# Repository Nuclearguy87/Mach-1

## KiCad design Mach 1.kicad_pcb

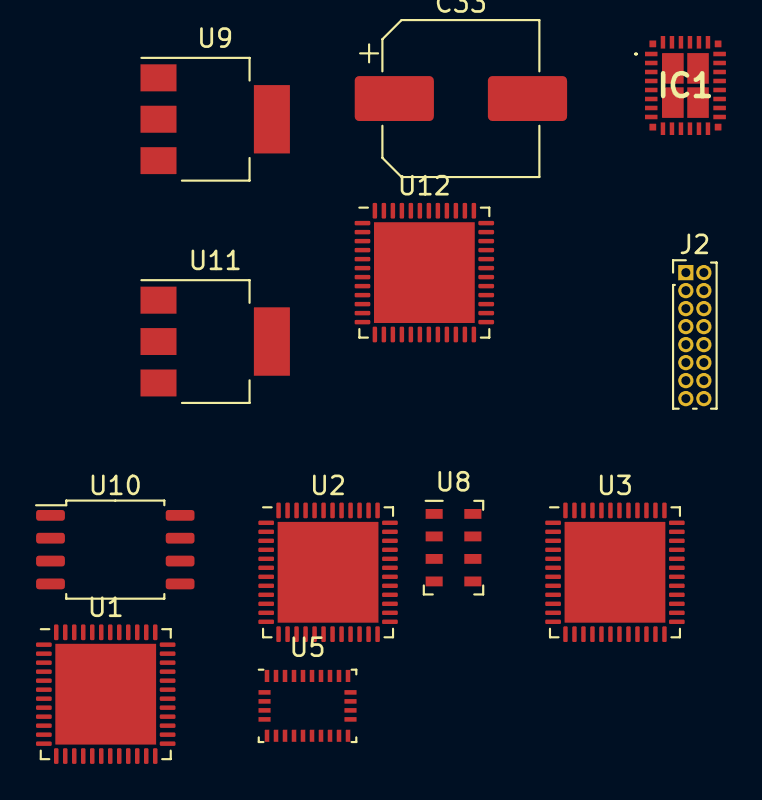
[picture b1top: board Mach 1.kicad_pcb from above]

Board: 2 copper layers, 12 parts (0 on the bottom side), 13 nets, no tracks yet.

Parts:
C33: 220m; CP_Elec_8x10.5
IC1: LT8638SJV#TRPBF; LT8638SJVTRPBF
J2: Conn_02x08_Counter_Clockwise; PinHeader_2x08_P1.00mm_Vertical
U1: STM32U575CIU6Q; QFN-48-1EP_7x7mm_P0.5mm_EP5.6x5.6mm
U2, U3, U12: STM32L552CCU6; QFN-48-1EP_7x7mm_P0.5mm_EP5.6x5.6mm
U5: BNO055; LGA-28_5.2x3.8mm_P0.5mm
U8: MS5611-01BA; LGA-8_3x5mm_P1.25mm
U9, U11: LM1117MPX-3.3; SOT-223-3_TabPin2
U10: W25Q128JVS; SOIC-8_5.23x5.23mm_P1.27mm

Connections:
+3.3V: IC1.2 (BIAS), J2.8, U1.21 (VDDSMPS), U1.25 (VDD), U1.36 (VDD), U1.48 (VDD), U2.24 (VDD), U2.36 (VDD), U2.48 (VDD), U3.24 (VDD), U3.36 (VDD), U3.48 (VDD), U5.3 (VDD), U5.28 (VDDIO), U8.1 (VDD), U8.2 (PS), U10.8 (VCC)
+3.3VA: U1.9 (VDDA), U2.9 (VDDA), U3.9 (VDDA)
/Controll/VBB: C33.1, U12.1 (VBAT)
/Motion/B5_SCL: U2.30 (PA9), U5.19 (COM1)
/Motion/B5_SDA: U2.31 (PA10), U5.20 (COM0)
/Motion/M5_SCL: U2.21 (PB10), U8.8 (SCLK)
/Motion/M5_SDA: U2.22 (PB11), U8.7 (SDI/SDA)
/PSU/INTVCC: IC1.3 (INTVCC), IC1.24 (SYNC/MODE)
/PSU/SW: IC1.5 (SW_1), IC1.6 (SW_2), IC1.7 (SW_3), IC1.8 (SW_4)
/VDD11: U1.23 (VDD11), U1.46 (VDD11)
GND: C33.2, IC1.9 (GND_1), IC1.10 (GND_2), IC1.11 (GND_3), IC1.12 (GND_4), IC1.13 (GND_5), IC1.14 (GND_6), IC1.20 (GND_7), IC1.29 (GND_8), IC1.30 (GND_9), IC1.31 (GND_10), IC1.32 (GND_11), IC1.33 (GND_12), IC1.34 (GND_13), IC1.35 (GND_14), IC1.36 (GND_15), J2.9, U1.8 (VSSA), U1.22 (VSSSMPS), U1.24 (VSS), U1.35 (VSS), U1.47 (VSS), U1.49 (VSS), U2.8 (VSSA), U2.23 (VSS), U2.35 (VSS), U2.47 (VSS), U2.49 (VSS), U3.8 (VSSA), U3.23 (VSS), U3.35 (VSS), U3.47 (VSS), U3.49 (VSS), U5.2 (GND), U5.5 (PS1), U5.6 (PS0), U5.15 (GNDIO), U5.16 (GNDIO), U5.17 (COM3), U5.18 (COM2), U5.25 (GNDIO), U8.3 (GND), U8.4 (CSB), U8.5 (CSB), U9.1 (GND), U10.4 (GND), U11.1 (GND), U12.8 (VSSA), U12.23 (VSS), U12.35 (VSS), U12.47 (VSS), U12.49 (VSS)
VBACK: U1.1 (VBAT), U2.1 (VBAT), U3.1 (VBAT), U9.2 (VO), U11.2 (VO), U12.24 (VDD), U12.36 (VDD), U12.48 (VDD)
VBAT: IC1.15 (VIN_1), IC1.16 (VIN_2), IC1.17 (VIN_3), IC1.18 (VIN_4), J2.7, U9.3 (VI), U11.3 (VI)

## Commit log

2024-01-25 Initial Work
